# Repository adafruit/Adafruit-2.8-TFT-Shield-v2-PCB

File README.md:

# Adafruit 2.8 TFT LCD Display Shield v2 PCBs
&nbsp; 
<br />
Click to view/purchase from the Adafruit Shop:
- [2.8" TFT Touch Shield for Arduino with Resistive Touch Screen](https://www.adafruit.com/product/1651)
- [2.8" TFT Touch Shield for Arduino w/Capacitive Touch](https://www.adafruit.com/product/1947)

Spice up your Arduino project with a beautiful large touchscreen display shield with built in microSD card connection. This TFT display is big (2.8" diagonal) bright (4 white-LED backlight) and colorful (18-bit 262,000 different shades)! 240x320 pixels with individual pixel control. It has way more resolution than a black and white 128x64 display. As a bonus, these displays has a resistive or capacitive touchscreen attached to it already, so you can detect finger presses anywhere on the screen. 

We've updated our original v1 shield to an SPI display - its a tiny bit slower but uses a lot less pins and is now much easier to use with Mega & Leonardo. We also include an SPI touchscreen controller so you only need one additional pin to add a high quality touchscreen controller. Even with all the extras, the price is lower thanks to our parts sourcing & engineering skillz!

This is the PCB for the two Adafruit 2.8" TFT Shields v2 Resistive and Capacitive touch screens. 

The format is EagleCAD schematic and board layout

For more details, check out the product pages at

- https://www.adafruit.com/product/1651
- https://www.adafruit.com/product/1947

### License

Adafruit invests time and resources providing this open source design, please support Adafruit and open-source hardware by [purchasing products from Adafruit](https://www.adafruit.com)!

All text above must be included in any redistribution

Designed by Limor Fried/Ladyada for Adafruit Industries.
Creative Commons Attribution/Share-Alike, all text above must be included in any redistribution. 
See license.txt for additional information.

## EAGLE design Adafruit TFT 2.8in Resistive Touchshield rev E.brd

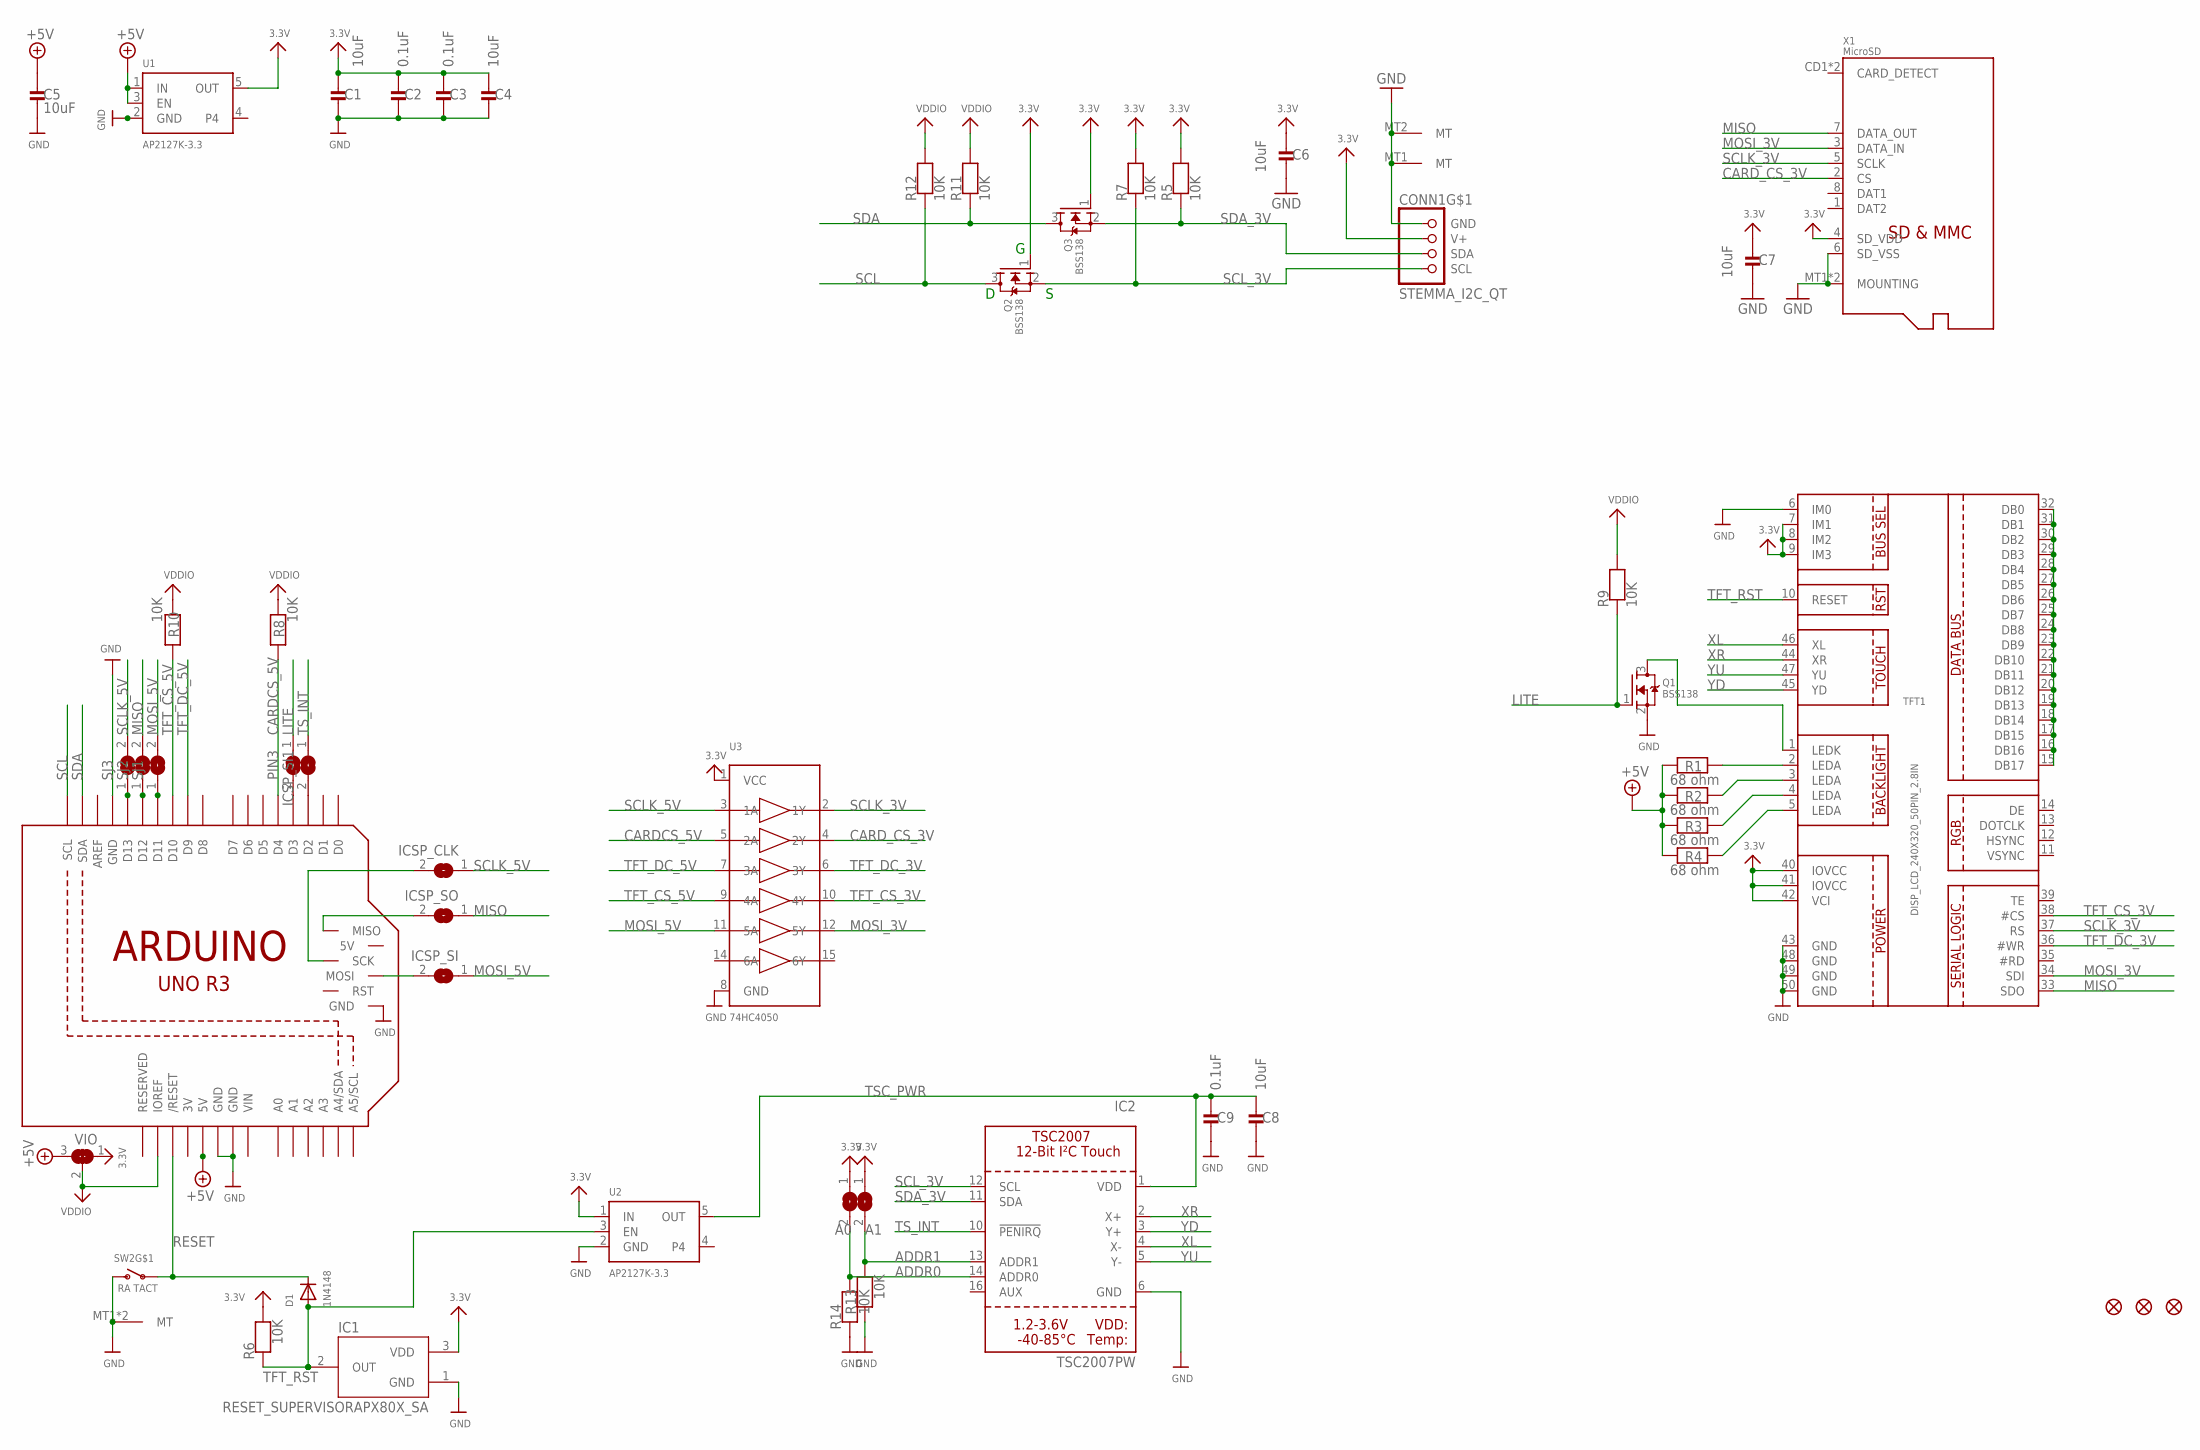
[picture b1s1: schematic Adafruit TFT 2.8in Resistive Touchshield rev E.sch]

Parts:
ARD: ARDUINO_R3_ICSPSMT; ARDUINOR3_ICSP_SMT
C1, C4, C5, C6, C7, C8: 10uF; 0805-NO
C2, C3, C9: 0.1uF; 0603-NO
CONN1: STEMMA_I2C_QT; JST_SH4
D1: 1N4148; SOD-323F
IC1: RESET_SUPERVISORAPX80X_SA; SOT23-WIDE
IC2: TSC2007PW; TSSOP16
ICSP_CLK: SOLDERJUMPERCLOSED; SOLDERJUMPER_CLOSEDWIRE
ICSP_CLK1: A1; SOLDERJUMPER_ARROW_NOPASTE
ICSP_CLK2: A0; SOLDERJUMPER_ARROW_NOPASTE
ICSP_SI, ICSP_SI1: SOLDERJUMPERCLOSED; SOLDERJUMPER_CLOSEDWIRE
ICSP_SO: SOLDERJUMPERCLOSED; SOLDERJUMPER_CLOSEDWIRE
PIN3: SOLDERJUMPER; SOLDERJUMPER_ARROW_NOPASTE
Q1, Q2, Q3: BSS138; SOT23-WIDE
R1, R2, R3, R4: 68 ohm; 0603-NO
R5, R6, R7, R8, R9, R10, R11, R12, R13, R14: 10K; 0603-NO
SJ1, SJ2, SJ3: SOLDERJUMPER; SOLDERJUMPER_ARROW_NOPASTE
SW2: RA TACT; SPST_TACTILE_RA
TFT1: DISP_LCD_240X320_50PIN_2.8IN; TFT_2.83IN_240X320_50PIN
U1, U2: AP2127K-3.3; SOT23-5
U3: 74HC4050; SOIC16
U$10, U$11, U$19: FIDUCIAL_1MM
VIO: SOLDERJUMPER_2WAY; SOLDERJUMPER_2WAY_OPEN_NOPASTE
X1: MicroSD; MICROSD

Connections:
3.3V: C1.1, C2.1, C3.1, C4.1, C6.1, C7.1, CONN1.2 (V+), IC1.3 (VDD), ICSP_CLK1.1, ICSP_CLK2.1, Q2.1 (G), Q3.1 (G), R5.2, R6.2, R7.2, TFT1.7 (IM1), TFT1.8 (IM2), TFT1.9 (IM3), TFT1.40 (IOVCC), TFT1.41 (IOVCC), TFT1.42 (VCI), U1.5 (OUT), U2.1 (IN), U3.1 (VCC), VIO.1, X1.4 (SD_VDD)
3V: ARD.3V
+5V: ARD.5V, C5.1, R1.1, R2.1, R3.1, R4.1, U1.1 (IN), U1.3 (EN), VIO.3
ADDR0: IC2.14 (ADDR0), ICSP_CLK2.2, R14.2
ADDR1: IC2.13 (ADDR1), ICSP_CLK1.2, R13.2
BACKLITE: ARD.D3, PIN3.2
CARDCS_5V: ARD.D4, R8.1, U3.5 (2A)
CARD_CS_3V: U3.4 (2Y), X1.2 (CS)
GND: ARD.GND, ARD.GND@1 (GND), ARD.GND@2 (GND), ARD.GND@3 (GND), C1.2, C2.2, C3.2, C4.2, C5.2, C6.2, C7.2, C8.2, C9.2, CONN1.1 (GND), CONN1.MT1 (MT), CONN1.MT2 (MT), IC1.1 (GND), IC2.6 (GND), Q1.2 (S), R13.1, R14.1, SW2.2 (S), SW2.MT1 (MT), SW2.MT2 (MT), TFT1.6 (IM0), TFT1.43 (GND), TFT1.48 (GND), TFT1.49 (GND), TFT1.50 (GND), U1.2 (GND), U2.2 (GND), U3.8 (GND), X1.6 (SD_VSS), X1.MT1 (MOUNTING), X1.MT2 (MOUNTING)
LITE: PIN3.1, Q1.1 (G), R9.1
MISO: ICSP_SO.1, SJ2.2, TFT1.33 (SDO), X1.7 (DATA_OUT)
MOSI_3V: TFT1.34 (SDI), U3.12 (5Y), X1.3 (DATA_IN)
MOSI_5V: ICSP_SI.1, SJ1.2, U3.11 (5A)
unnamed: Q1.3 (D), TFT1.1 (LEDK)
unnamed: R1.2, TFT1.2 (LEDA)
unnamed: R2.2, TFT1.3 (LEDA)
unnamed: R3.2, TFT1.4 (LEDA)
unnamed: ARD.MOSI, ICSP_SI.2
unnamed: ARD.D2, ICSP_SI1.2
unnamed: TFT1.15 (DB17), TFT1.16 (DB16), TFT1.17 (DB15), TFT1.18 (DB14), TFT1.19 (DB13), TFT1.20 (DB12), TFT1.21 (DB11), TFT1.22 (DB10), TFT1.23 (DB9), TFT1.24 (DB8), TFT1.25 (DB7), TFT1.26 (DB6), TFT1.27 (DB5), TFT1.28 (DB4), TFT1.29 (DB3), TFT1.30 (DB2), TFT1.31 (DB1), TFT1.32 (DB0)
unnamed: R4.2, TFT1.5 (LEDA)
unnamed: ARD.MISO, ICSP_SO.2
unnamed: ARD.SCK, ICSP_CLK.2
unnamed: ARD.D13, SJ3.1
unnamed: ARD.D12, SJ2.1
unnamed: ARD.D11, SJ1.1
RESET: ARD.RESET (/RESET), D1.C, SW2.1
SCL: ARD.SCL, Q2.3 (D), R12.1
SCLK_3V: TFT1.37 (RS), U3.2 (1Y), X1.5 (SCLK)
SCLK_5V: ICSP_CLK.1, SJ3.2, U3.3 (1A)
SCL_3V: CONN1.4 (SCL), IC2.12 (SCL), Q2.2 (S), R7.1
SDA: ARD.SDA, Q3.3 (D), R11.1
SDA_3V: CONN1.3 (SDA), IC2.11 (SDA), Q3.2 (S), R5.1
TFT_CS_3V: TFT1.38 (#CS), U3.10 (4Y)
TFT_CS_5V: ARD.D10, R10.1, U3.9 (4A)
TFT_DC_3V: TFT1.36 (#WR), U3.6 (3Y)
TFT_DC_5V: ARD.D9, U3.7 (3A)
TFT_RST: D1.A, IC1.2 (OUT), R6.1, TFT1.10 (RESET), U2.3 (EN)
TSC_PWR: C8.1, C9.1, IC2.1 (VDD), U2.5 (OUT)
TS_INT: IC2.10 (!PENIRQ), ICSP_SI1.1
VDDIO: ARD.IOREF, R8.2, R9.2, R10.2, R11.2, R12.2, VIO.2
VIN: ARD.VIN
XL: IC2.4 (X-), TFT1.46 (XL)
XR: IC2.2 (X+), TFT1.44 (XR)
YD: IC2.3 (Y+), TFT1.45 (YD)
YU: IC2.5 (Y-), TFT1.47 (YU)

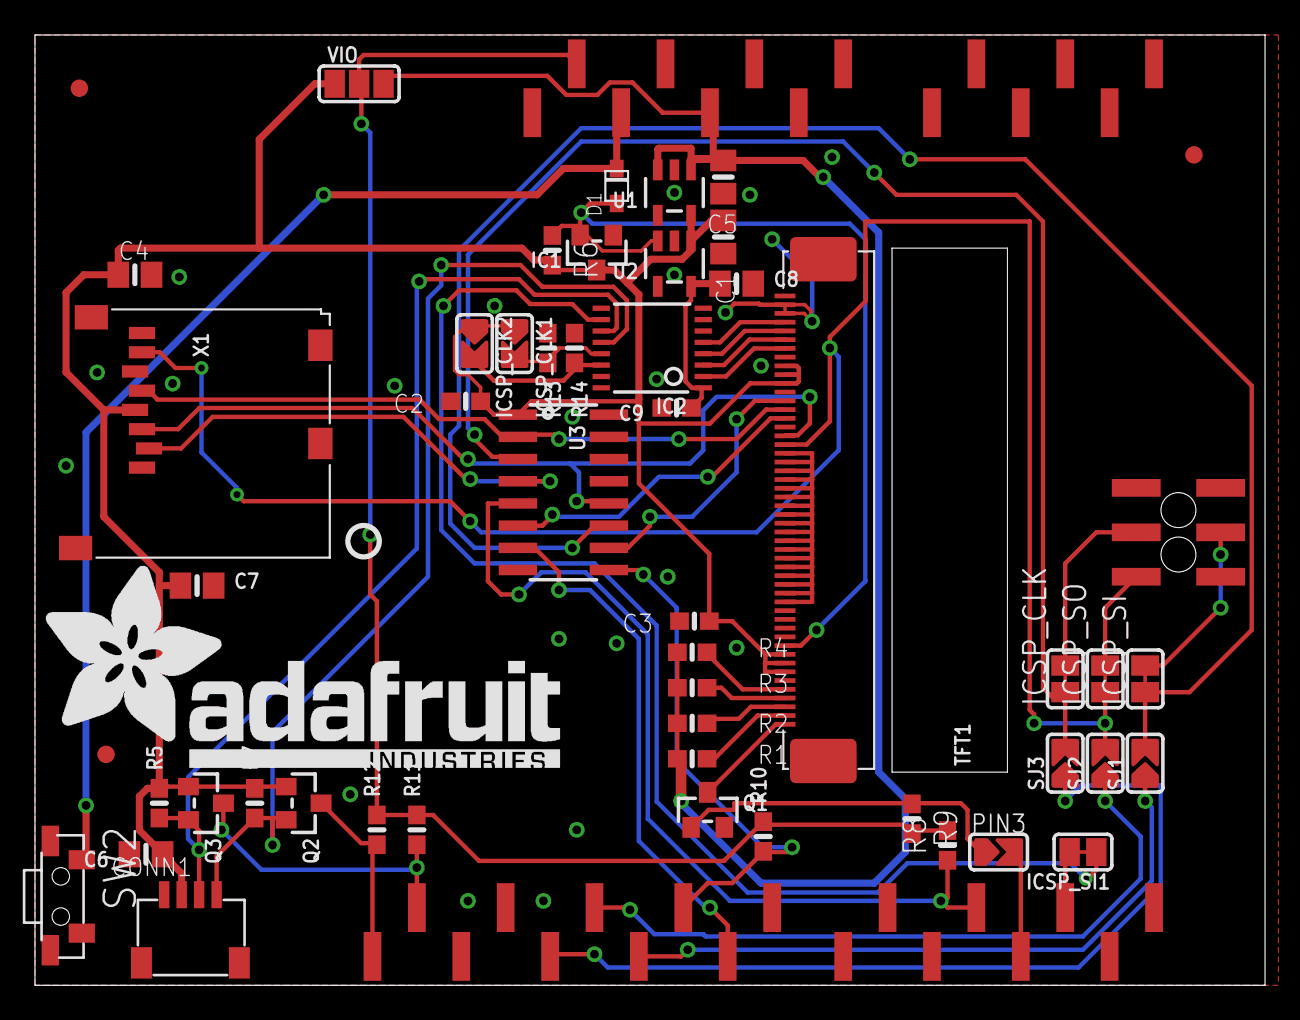
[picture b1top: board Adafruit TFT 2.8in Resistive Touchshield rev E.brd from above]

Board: 2 copper layers, 70.4 x 54.4 mm, 76 parts (2 on the bottom side), 44 nets.

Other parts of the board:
PLABEL0: PLABEL0
PLABEL1: PLABEL1
PLABEL2: PLABEL2
PLABEL3: PLABEL3
PLABEL4: PLABEL4
PLABEL5: PLABEL5
PLABEL6: PLABEL6
PLABEL7: PLABEL7
PLABEL8: PLABEL8
PLABEL9: PLABEL9
PLABEL10: PLABEL10
PLABEL11: PLABEL11
PLABEL12: PLABEL12
PLABEL13: PLABEL13
PLABEL14: PLABEL14
PLABEL15: PLABEL15
PLABEL16: PLABEL16
PLABEL17: PLABEL17
PLABEL18: PLABEL18
PLABEL19: PLABEL19
PLABEL20: PLABEL20
PLABEL21: PLABEL21
PLABEL22: PLABEL22
U$3: PCBFEAT-REV-040
U$20: ADAFRUIT_TEXT_30MM

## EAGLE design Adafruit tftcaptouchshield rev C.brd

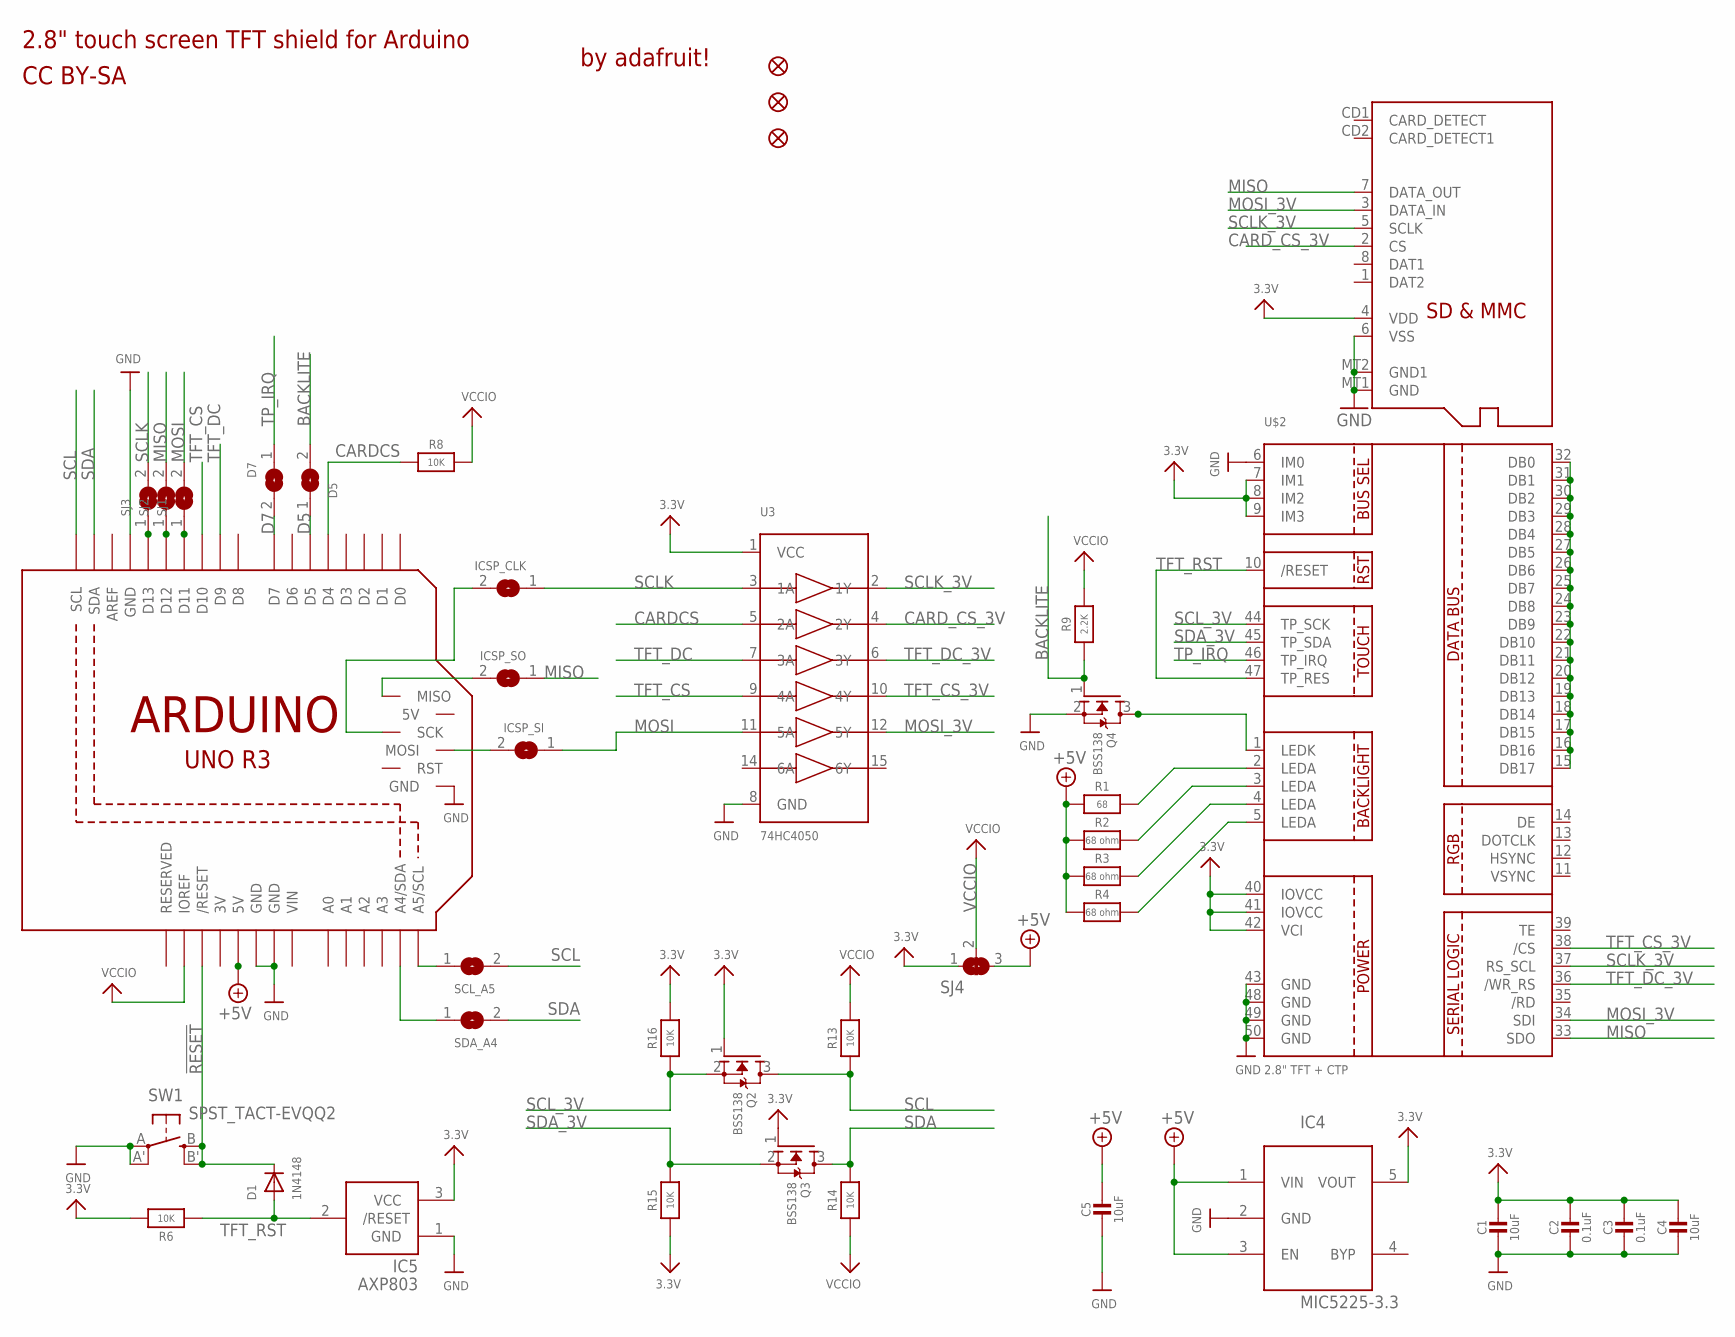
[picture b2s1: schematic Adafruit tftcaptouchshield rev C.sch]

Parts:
C1, C4, C5: 10uF; 0805-NO
C2, C3: 0.1uF; 0805-NO
D1: 1N4148; SOD-323F
D5, D7: SOLDERJUMPER; SOLDERJUMPER_ARROW_NOPASTE
IC4: MIC5225-3.3; SOT23-5L
IC5: AXP803; SOT23
ICSP_CLK: SOLDERJUMPERCLOSED; SOLDERJUMPER_CLOSEDWIRE
ICSP_SI: SOLDERJUMPERCLOSED; SOLDERJUMPER_CLOSEDWIRE
ICSP_SO: SOLDERJUMPERCLOSED; SOLDERJUMPER_CLOSEDWIRE
Q2, Q3, Q4: BSS138; SOT23-WIDE
R1: 68; 0805-NO
R2, R3, R4: 68 ohm; 0805-NO
R6, R8, R13, R14, R15, R16: 10K; 0805-NO
R9: 2.2K; 0805-NO
SCL_A5: SOLDERJUMPERREFLOW_NOPASTE; SOLDERJUMPER_REFLOW_NOPASTE
SDA_A4: SOLDERJUMPERREFLOW_NOPASTE; SOLDERJUMPER_REFLOW_NOPASTE
SJ1, SJ2, SJ3: SOLDERJUMPER; SOLDERJUMPER_ARROW_NOPASTE
SJ4: SOLDERJUMPER_2WAY; SOLDERJUMPER_2WAY_OPEN_NOPASTE
SW1: SPST_TACT-EVQQ2; EVQ-Q2
U3: 74HC4050; SOIC16
U$2: 2.8" TFT + CTP; TFT_2.83IN_240X320_50PIN
U$3: MICROSD
U$10, U$11, U$19: FIDUCIAL_1MM
U$17: ARDUINO_R3_ICSPSMT; ARDUINOR3_ICSP_SMT

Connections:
3.3V: C1.1, C2.1, C3.1, C4.1, IC4.5 (VOUT), IC5.3 (VCC), Q2.1 (G), Q3.1 (G), R6.2, R15.1, R16.2, SJ4.1, U3.1 (VCC), U$2.7 (IM1), U$2.8 (IM2), U$2.9 (IM3), U$2.40 (IOVCC), U$2.41 (IOVCC), U$2.42 (VCI), U$3.4 (VDD)
3V: U$17.3V
!RESET: D1.C, SW1.B (S), SW1.B' (S1), U$17.RESET (/RESET)
+5V: C5.1, IC4.1 (VIN), IC4.3 (EN), R1.1, R2.1, R3.1, R4.1, SJ4.3, U$17.5V
BACKLITE: D5.2, Q4.1 (G), R9.1
CARDCS: R8.1, U3.5 (2A), U$17.D4
CARD_CS_3V: U3.4 (2Y), U$3.2 (CS)
D5: D5.1, U$17.D5
D7: D7.2, U$17.D7
GND: C1.2, C2.2, C3.2, C4.2, C5.2, IC4.2 (GND), IC5.1 (GND), Q4.2 (S), SW1.A, SW1.A' (P1), U3.8 (GND), U$2.6 (IM0), U$2.43 (GND), U$2.48 (GND), U$2.49 (GND), U$2.50 (GND), U$3.6 (VSS), U$3.MT1 (GND), U$3.MT2 (GND1), U$17.GND, U$17.GND@1 (GND), U$17.GND@2 (GND), U$17.GND@3 (GND)
MISO: ICSP_SO.1, SJ2.2, U$2.33 (SDO), U$3.7 (DATA_OUT)
MOSI: ICSP_SI.1, SJ1.2, U3.11 (5A)
MOSI_3V: U3.12 (5Y), U$2.34 (SDI), U$3.3 (DATA_IN)
unnamed: Q4.3 (D), U$2.1 (LEDK)
unnamed: R1.2, U$2.2 (LEDA)
unnamed: R2.2, U$2.3 (LEDA)
unnamed: R3.2, U$2.4 (LEDA)
unnamed: ICSP_SI.2, U$17.MOSI
unnamed: U$2.15 (DB17), U$2.16 (DB16), U$2.17 (DB15), U$2.18 (DB14), U$2.19 (DB13), U$2.20 (DB12), U$2.21 (DB11), U$2.22 (DB10), U$2.23 (DB9), U$2.24 (DB8), U$2.25 (DB7), U$2.26 (DB6), U$2.27 (DB5), U$2.28 (DB4), U$2.29 (DB3), U$2.30 (DB2), U$2.31 (DB1), U$2.32 (DB0)
unnamed: R4.2, U$2.5 (LEDA)
unnamed: ICSP_SO.2, U$17.MISO
unnamed: ICSP_CLK.2, U$17.SCK
unnamed: SJ3.1, U$17.D13
unnamed: SJ2.1, U$17.D12
unnamed: SJ1.1, U$17.D11
unnamed: SDA_A4.1, U$17.A4 (A4/SDA)
unnamed: SCL_A5.1, U$17.A5 (A5/SCL)
SCL: Q2.3 (D), R13.1, SCL_A5.2, U$17.SCL
SCLK: ICSP_CLK.1, SJ3.2, U3.3 (1A)
SCLK_3V: U3.2 (1Y), U$2.37 (RS_SCL), U$3.5 (SCLK)
SCL_3V: Q2.2 (S), R16.1, U$2.44 (TP_SCK)
SDA: Q3.3 (D), R14.2, SDA_A4.2, U$17.SDA
SDA_3V: Q3.2 (S), R15.2, U$2.45 (TP_SDA)
TFT_CS: U3.9 (4A), U$17.D10
TFT_CS_3V: U3.10 (4Y), U$2.38 (/CS)
TFT_DC: U3.7 (3A), U$17.D9
TFT_DC_3V: U3.6 (3Y), U$2.36 (/WR_RS)
TFT_RST: D1.A, IC5.2 (/RESET), R6.1, U$2.10 (/RESET), U$2.47 (TP_RES)
TP_IRQ: D7.1, U$2.46 (TP_IRQ)
VCCIO: R8.2, R9.2, R13.2, R14.1, SJ4.2, U$17.IOREF
VIN: U$17.VIN

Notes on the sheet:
2.8" touch screen TFT shield for Arduino
by adafruit!
CC BY-SA

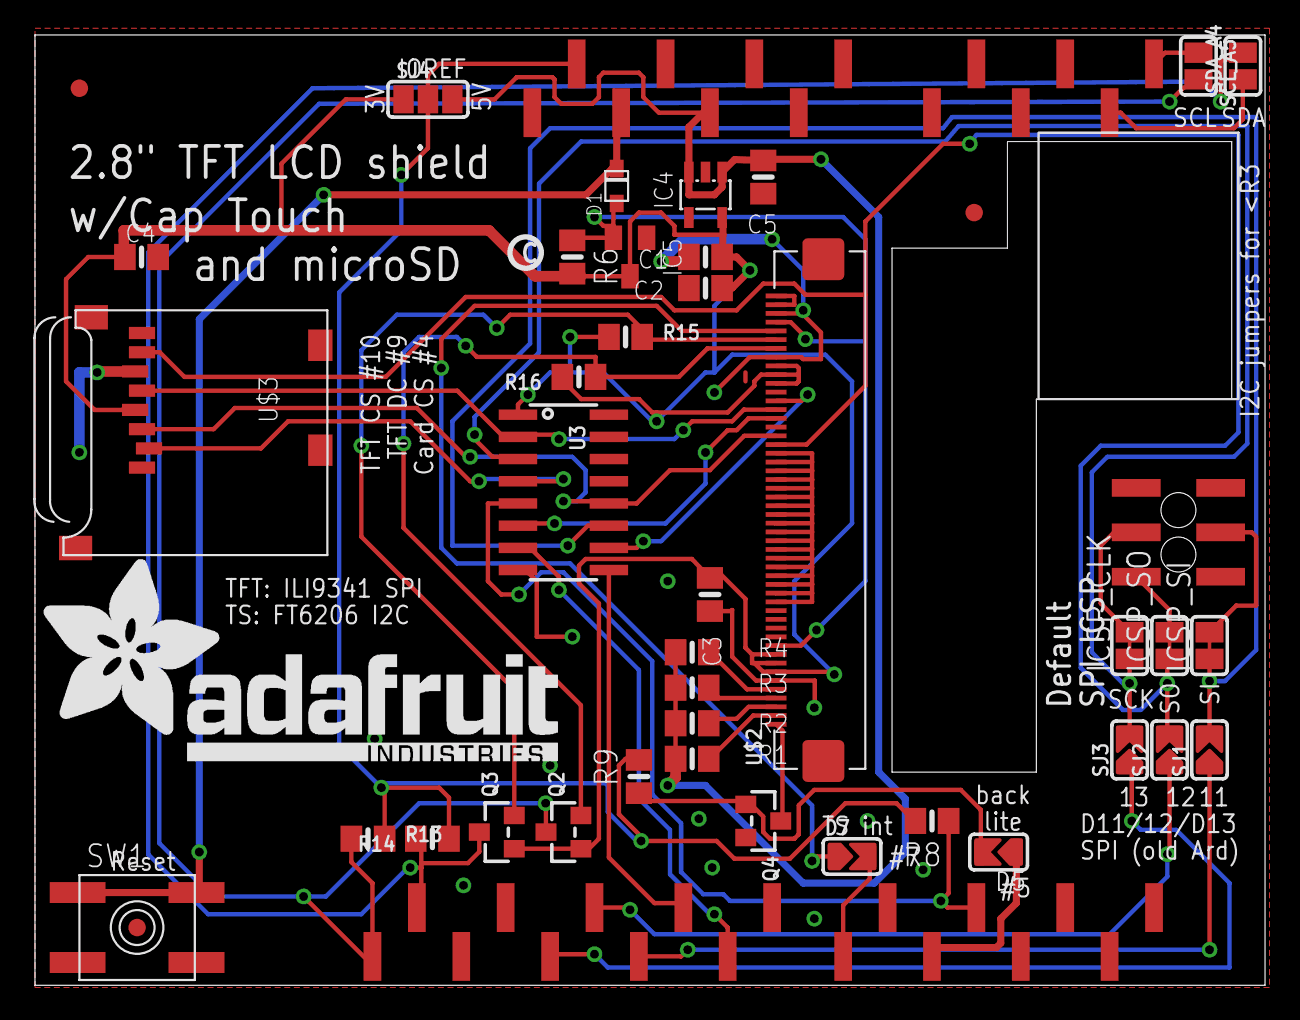
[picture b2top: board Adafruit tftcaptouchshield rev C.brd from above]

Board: 2 copper layers, 70.2 x 54.2 mm, 43 parts (2 on the bottom side), 39 nets.

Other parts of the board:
U$7: PCBFEAT-REV-040
U$20: ADAFRUIT_TEXT_30MM

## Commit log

2014-08-17 init
2014-08-27 captouch
2014-08-27 added url
2019-08-23 Updated to latest versions
2023-09-11 adding rev E files
